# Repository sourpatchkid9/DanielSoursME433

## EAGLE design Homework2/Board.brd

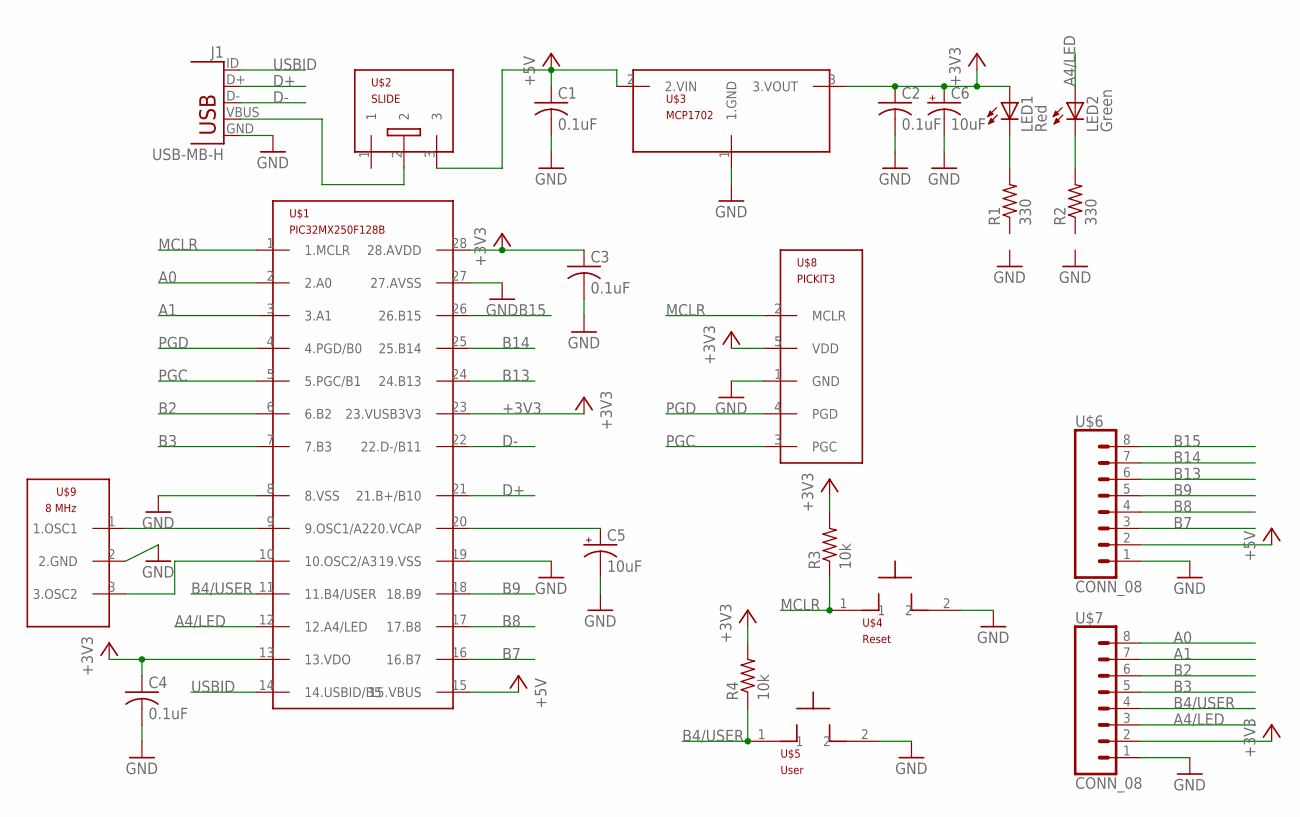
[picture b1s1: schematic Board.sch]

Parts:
C1, C2, C3, C4: 0.1uF; C025-025X050
C5, C6: 10uF; B45181B
J1: USB-MB-H
LED1: Red; LED3MM
LED2: Green; LED3MM
R1, R2: 330; 0207/10
R3, R4: 10k; 0207/10
U$1: PIC32MX250F128B; DIL28-3
U$2: SLIDE
U$3: MCP1702; TO92
U$4: Reset; PB
U$5: User; PB
U$6, U$7: CONN_08; 1X08
U$8: PICKIT3; 1X05
U$9: 8 MHz; OSC

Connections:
+3V3: C2.1, C3.1, C4.1, C6.+, LED1.A, R3.2, R4.2, U$1.13 (13.VDO), U$1.23 (23.VUSB3V3), U$1.28 (28.AVDD), U$3.3 (3.VOUT), U$7.2, U$8.5 (VDD)
+5V: C1.1, U$1.15 (15.VBUS), U$2.3, U$3.2 (2.VIN), U$6.2
A0: U$1.2 (2.A0), U$7.8
A1: U$1.3 (3.A1), U$7.7
A4/LED: LED2.A, U$1.12 (12.A4/LED), U$7.3
B2: U$1.6 (6.B2), U$7.6
B3: U$1.7 (7.B3), U$7.5
B4/USER: R4.1, U$1.11 (11.B4/USER), U$5.1, U$7.4
B7: U$1.16 (16.B7), U$6.3
B8: U$1.17 (17.B8), U$6.4
B9: U$1.18 (18.B9), U$6.5
B13: U$1.24 (24.B13), U$6.6
B14: U$1.25 (25.B14), U$6.7
B15: U$1.26 (26.B15), U$6.8
D+: J1.D+, U$1.21 (21.B+/B10)
D-: J1.D-, U$1.22 (22.D-/B11)
GND: C1.2, C2.2, C3.2, C4.2, C5.-, C6.-, J1.GND, U$1.8 (8.VSS), U$1.19 (19.VSS), U$1.27 (27.AVSS), U$3.1 (1.GND), U$4.2, U$5.2, U$6.1, U$7.1, U$8.1 (GND), U$9.2 (2.GND)
MCLR: R3.1, U$1.1 (1.MCLR), U$4.1, U$8.2 (MCLR)
unnamed: J1.VBUS, U$2.2
unnamed: U$1.9 (9.OSC1/A2), U$9.1 (1.OSC1)
unnamed: U$1.10 (10.OSC2/A3), U$9.3 (3.OSC2)
unnamed: LED1.K (C), R1.2
unnamed: LED2.K (C), R2.2
unnamed: C5.+, U$1.20 (20.VCAP)
PGC: U$1.5 (5.PGC/B1), U$8.3 (PGC)
PGD: U$1.4 (4.PGD/B0), U$8.4 (PGD)
USBID: J1.ID, U$1.14 (14.USBID/B5)

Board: 2 copper layers, 22 parts (0 on the bottom side), 27 nets, no tracks yet.

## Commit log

2017-03-30 :tada: Added .gitattributes & .gitignore files
2017-03-30 LED on
2017-03-30 Blink
2017-03-30 Everything is working
2017-03-30 Uploads
2017-04-04 Create New
2017-04-07 Create txt
2017-04-18 Homework 5
2017-04-18 I2C midway
2017-04-18 Working I2C
2017-04-18 Modified
2017-04-22 Finished LCD
2017-04-22 Remove extra
2017-04-22 IMU start
2017-04-25 IMU working
2017-05-01 Harmony Working
2017-05-01 IMU on Harmony
2017-05-01 Working Harmony IMU
2017-05-09 USB working
2017-05-23 Android Bar Working
2017-05-23 Camera All Green Lines FPS not working
2017-06-08 Final Project
